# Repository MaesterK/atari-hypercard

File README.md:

Atari VCS / 2600 Supercard with menu implemented for atari itself creating text based menu on the fly.
Uses programmable logic ic (GAL) as latch and nand chip to select and switch between images via adress bus. 
Works only with early ("dumb") images.

The assembly code for the menu build using DASM and the framework (mainly the definitions from vcs.h) from SvOlli's atari 2600 workshop (https://svolli.org/atari2600/)

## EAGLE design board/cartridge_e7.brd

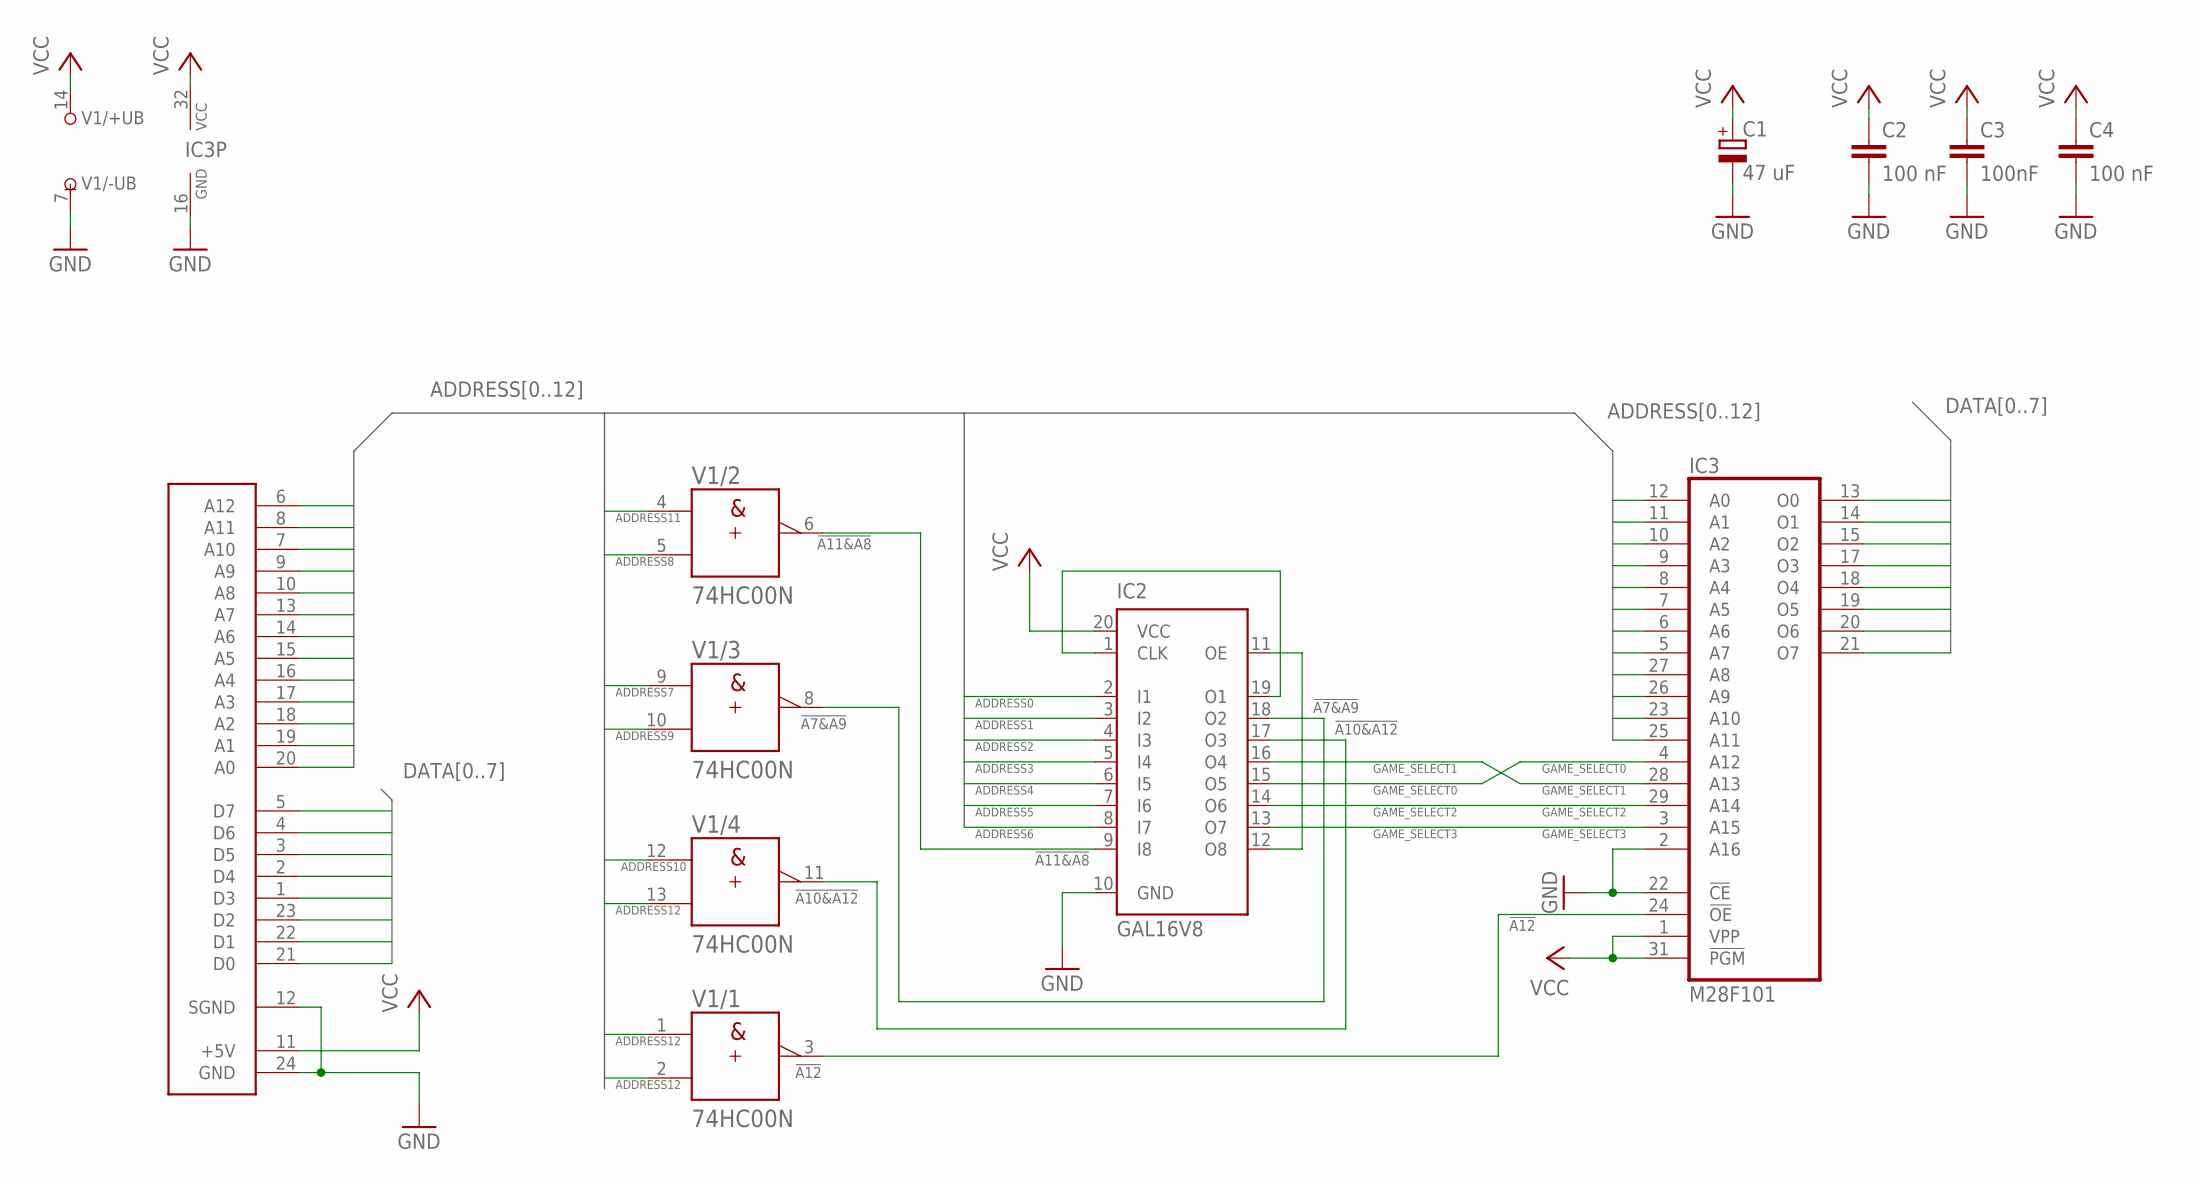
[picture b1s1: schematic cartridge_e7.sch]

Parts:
C1: 47 uF; E3,5-8
C2, C4: 100 nF; C050-024X044
C3: 100nF; C050-024X044
CONN1: 24POSCELARGE; 2600LARGE
IC2: GAL16V8; DIL20
IC3: M28F101; DIL32
V1: 74HC00N; DIL14

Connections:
!A7&A9: IC2.18 (O2), V1.8 (Y)
!A10&A12: IC2.17 (O3), V1.11 (Y)
!A11&A8: IC2.9 (I8), V1.6 (Y)
!A12: IC3.24 (!OE), V1.3 (Y)
ADDRESS0: CONN1.20 (A0), IC2.2 (I1), IC3.12 (A0)
ADDRESS1: CONN1.19 (A1), IC2.3 (I2), IC3.11 (A1)
ADDRESS2: CONN1.18 (A2), IC2.4 (I3), IC3.10 (A2)
ADDRESS3: CONN1.17 (A3), IC2.5 (I4), IC3.9 (A3)
ADDRESS4: CONN1.16 (A4), IC2.6 (I5), IC3.8 (A4)
ADDRESS5: CONN1.15 (A5), IC2.7 (I6), IC3.7 (A5)
ADDRESS6: CONN1.14 (A6), IC2.8 (I7), IC3.6 (A6)
ADDRESS7: CONN1.13 (A7), IC3.5 (A7), V1.9 (A)
ADDRESS8: CONN1.10 (A8), IC3.27 (A8), V1.5 (B)
ADDRESS9: CONN1.9 (A9), IC3.26 (A9), V1.10 (B)
ADDRESS10: CONN1.7 (A10), IC3.23 (A10), V1.12 (A)
ADDRESS11: CONN1.8 (A11), IC3.25 (A11), V1.4 (A)
ADDRESS12: CONN1.6 (A12), V1.1 (A), V1.2 (B), V1.13 (B)
DATA0: CONN1.21 (D0), IC3.13 (O0)
DATA1: CONN1.22 (D1), IC3.14 (O1)
DATA2: CONN1.23 (D2), IC3.15 (O2)
DATA3: CONN1.1 (D3), IC3.17 (O3)
DATA4: CONN1.2 (D4), IC3.18 (O4)
DATA5: CONN1.3 (D5), IC3.19 (O5)
DATA6: CONN1.4 (D6), IC3.20 (O6)
DATA7: CONN1.5 (D7), IC3.21 (O7)
GAME_SELECT0: IC2.15 (O5), IC3.4 (A12)
GAME_SELECT1: IC2.16 (O4), IC3.28 (A13)
GAME_SELECT2: IC2.14 (O6), IC3.29 (A14)
GAME_SELECT3: IC2.13 (O7), IC3.3 (A15)
GND: C1.-, C2.2, C3.2, C4.2, CONN1.12 (SGND), CONN1.24 (GND), IC2.10 (GND), IC3.2 (A16), IC3.16 (GND), IC3.22 (!CE), V1.7 (-UB)
unnamed: IC2.11 (OE), IC2.12 (O8)
unnamed: IC2.1 (CLK), IC2.19 (O1)
VCC: C1.+, C2.1, C3.1, C4.1, CONN1.11 (+5V), IC2.20 (VCC), IC3.1 (VPP), IC3.31 (!PGM), IC3.32 (VCC), V1.14 (+UB)

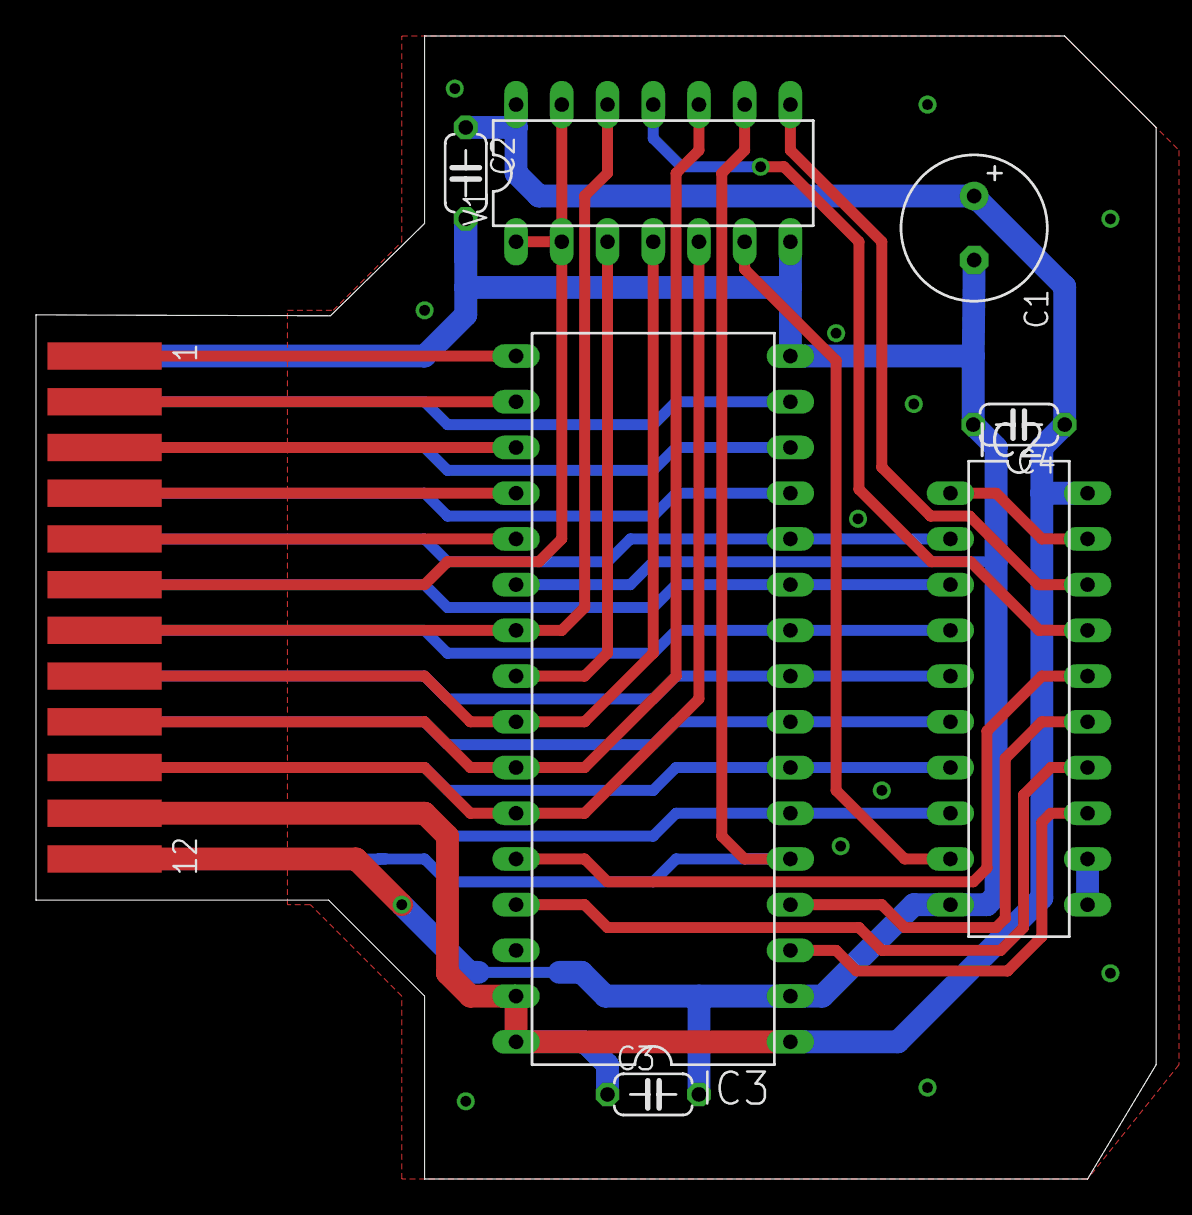
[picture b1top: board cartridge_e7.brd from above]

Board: 2 copper layers, 62.2 x 63.5 mm, 8 parts (0 on the bottom side), 33 nets.

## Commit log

2024-10-05 Add files via upload
    missing code for gal
